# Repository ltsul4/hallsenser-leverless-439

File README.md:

# Magnetic Leverless Controller (自作磁気接点レバーレス)

本プロジェクトは、磁気スイッチ（ホールセンサー）を採用した超低遅延・高機能な競技用レバーレスコントローラーの開発プロジェクトです。

卒業制作の一環として制作されており、進捗に合わせて随時コードやデータの更新を行います。

---

## 概要

従来の物理接点スイッチではなく、磁力による非接触検知を採用することで、物理的な摩耗を抑えつつ、ミリ単位での高度な入力制御を実現しています。

### 主な機能

* **ラピッドトリガー (Rapid Trigger)**
    指の上げ下げに即座に反応する超高速入力を実現。
* **可変作動点 (Actuation Point)**
    反応する深さを 0.1mm 単位でカスタマイズ可能。
* **Web Configurator**
    専用ソフト不要。ブラウザからリアルタイムに設定変更・モニタリングが可能。
* **SOCDクリーナー**
    競技ルールに準拠した同時押し処理（ニュートラル優先、後押し優先等）を実装。
* **コンボボタン機能**
    1つのボタンで複数のボタン同時押しを再現する補助機能（C1～C4）。
* **入力切断機能**
    設定中の誤入力を防ぐためのセーフティ機能。

---

## ハードウェア設計

設計データはすべて `PCB` フォルダ内に格納されています。

* **基板データ (PCB Design)**: 回路図および基板発注用のガーバーデータ。
* **筐体データ (Acrylic Case)**: レーザーカット用のアクリルパネル設計データ。

### 主要コンポーネント

* **MCU**: STM32F303CBT6
* **センサー**: GH39F ホールセンサー
* **スイッチ**: 
    * デフォルト: Gateron Magnetic Jade Ultra (3.2mmストローク)
    * 特別仕様: Gateron Magnetic Jade Pro (3.5mmストローク)
* **マルチプレクサ**: ADG708

> [!NOTE]
> 本リポジトリの標準ファームウェアは **3.2mmストローク (Jade Ultra)** に最適化されています。
> 3.5mmストロークのスイッチを使用する場合は、`main.c` 内の `TRAVEL_DISTANCE_MM` を `3.5f` に変更してビルドしてください。

---

## ディレクトリ構成

*(※必要に応じて追記してください)*

---

## 導入手順

### 1. ファームウェアの書き込み

1.  [STM32CubeProgrammer](https://www.st.com/ja/development-tools/stm32cubeprog.html) をダウンロードしてPCにインストールします。
2.  基板の裏面にある2つのボタンのうち、**上側のBOOTボタンを押しながら**PCとUSBケーブルで接続します。その後、STM32CubeProgrammerを起動します。
3.  画面右側の接続メニューから「USB」を選択し、「Port」のドロップダウンから適切なポート（例: `USB1`）を選んだ後、緑色の**「Connect」**ボタンをクリックして基板と接続します。

4.  接続が成功したら、画面左上の「Open file」タブをクリックします。
5.  ファイル選択ダイアログが開くので、ビルド済みの `.bin` ファイル（例: `Leverless_Controller.bin`）を選択して開きます。

6.  ファイルを読み込んだ後、「Download」ボタンをクリックしてファームウェアの書き込み（インストール）を実行します。
7.  **書き込み完了後、USBケーブルを一度抜き、ボタンを押さずにそのまま再度PCへ接続し直してください。**

### 2. 起動モードの選択

本デバイスには2つの動作モードがあります。

* **ゲームモード (通常起動)**
    そのままUSBを接続します。Windowsから「Xbox 360 Controller」として認識され、すぐにゲームで使用可能です。

* **設定モード (ボタン押下起動)**
    **UPボタン**を押しながらUSBを接続し、**数秒待ってから指を離します**。
    カスタムHIDデバイスとして認識され、ブラウザからの設定が可能になります。

### 3. Web Configurator による設定と使い方

1.  **設定モードで起動**
    前述の通り、UPボタンを押しながらデバイスをPCに接続します。
2.  **ブラウザで設定ページを開く**
    使用しているキースイッチに合わせて、以下のいずれかのページをブラウザ（Chrome/Edge推奨）で開きます。
    * **通常版 (3.2mm / Jade Ultra 等):** [WebDriver.htmlを開く](https://ltsul4.github.io/hallsenser-leverless-439/WebDriver/WebDriver.html)
    * **特別版 (3.5mm / Jade Pro 専用):** [WebDriver3.5.htmlを開く](https://ltsul4.github.io/hallsenser-leverless-439/WebDriver/WebDriver3.5.html)
3.  **デバイスの接続**
    画面右上の「接続」ボタンを押し、リストから該当する端末を選択して接続します。
    > ⚠️ **注意:** 端末選択画面で「Xbox 360 Controller」等の表示が出る場合は、設定モードでの接続が失敗しています。一度ケーブルを抜き、再度UPボタンを確実に押しながらつなぎ直してください。

4.  **各種設定の調整**
    接続が完了すると、専用ドライバー上で以下の設定が可能になります。
    * **キーマッピング:** 各ボタンへの入力割り当てを変更。
    * **入力感度の調整:** Actuation Point (AP: 作動点)、Rapid Trigger (RT: 感度)、Top/Bottom Deadzone (DZ: 指置き・底打ち時の誤爆防止) をスライダーで設定。
    * **リアルタイム動作:** 右下のグラフで、選択したボタン（画像ではUPボタン）のトラッキング状況をリアルタイムに確認。
    * **SOCD設定:** 画面上部のメニューからSOCDクリーナーの方式を選択。

5.  **同時押し設定 (コンボ機能)**
    画面を下にスクロールすると、C1～C4までの4種類の補助ボタンの設定項目があります。ここで複数ボタンの同時押しを登録することができます。
6.  **設定の保存**
    すべての設定が完了したら、画面右上の緑色の**「設定を保存」**ボタンを押します。
7.  **再起動して完了**
    保存完了後、**端末（USBケーブル）を一度抜き、そのまま再度つなぎ直す**ことで、設定がゲームモードに反映されます。

---

## 開発状況

- [x] ホールセンサーによるアナログ値の取得
- [x] ラピッドトリガー・可変作動点アルゴリズムの実装
- [x] WebHID / WebUSB による設定ツールの構築 (`WebDriver.html`)
- [x] Flashメモリへの設定保存機能
- [x] 同時押し（コンボ）ボタン機能の実装

---

## クレジット・参考元

本プロジェクトの制作にあたり、以下のプロジェクトを参考にさせていただきました。
* **参考元:** [kenyoshizoe/ember](https://github.com/kenyoshizoe/ember)

また、本プロジェクトのコードおよびドキュメントの一部は、**Gemini** を活用して作成されました。

---

## ライセンス

**MIT License**

本プロジェクトは卒業制作として継続的に開発されています。温かい目で見守っていただければ幸いです。

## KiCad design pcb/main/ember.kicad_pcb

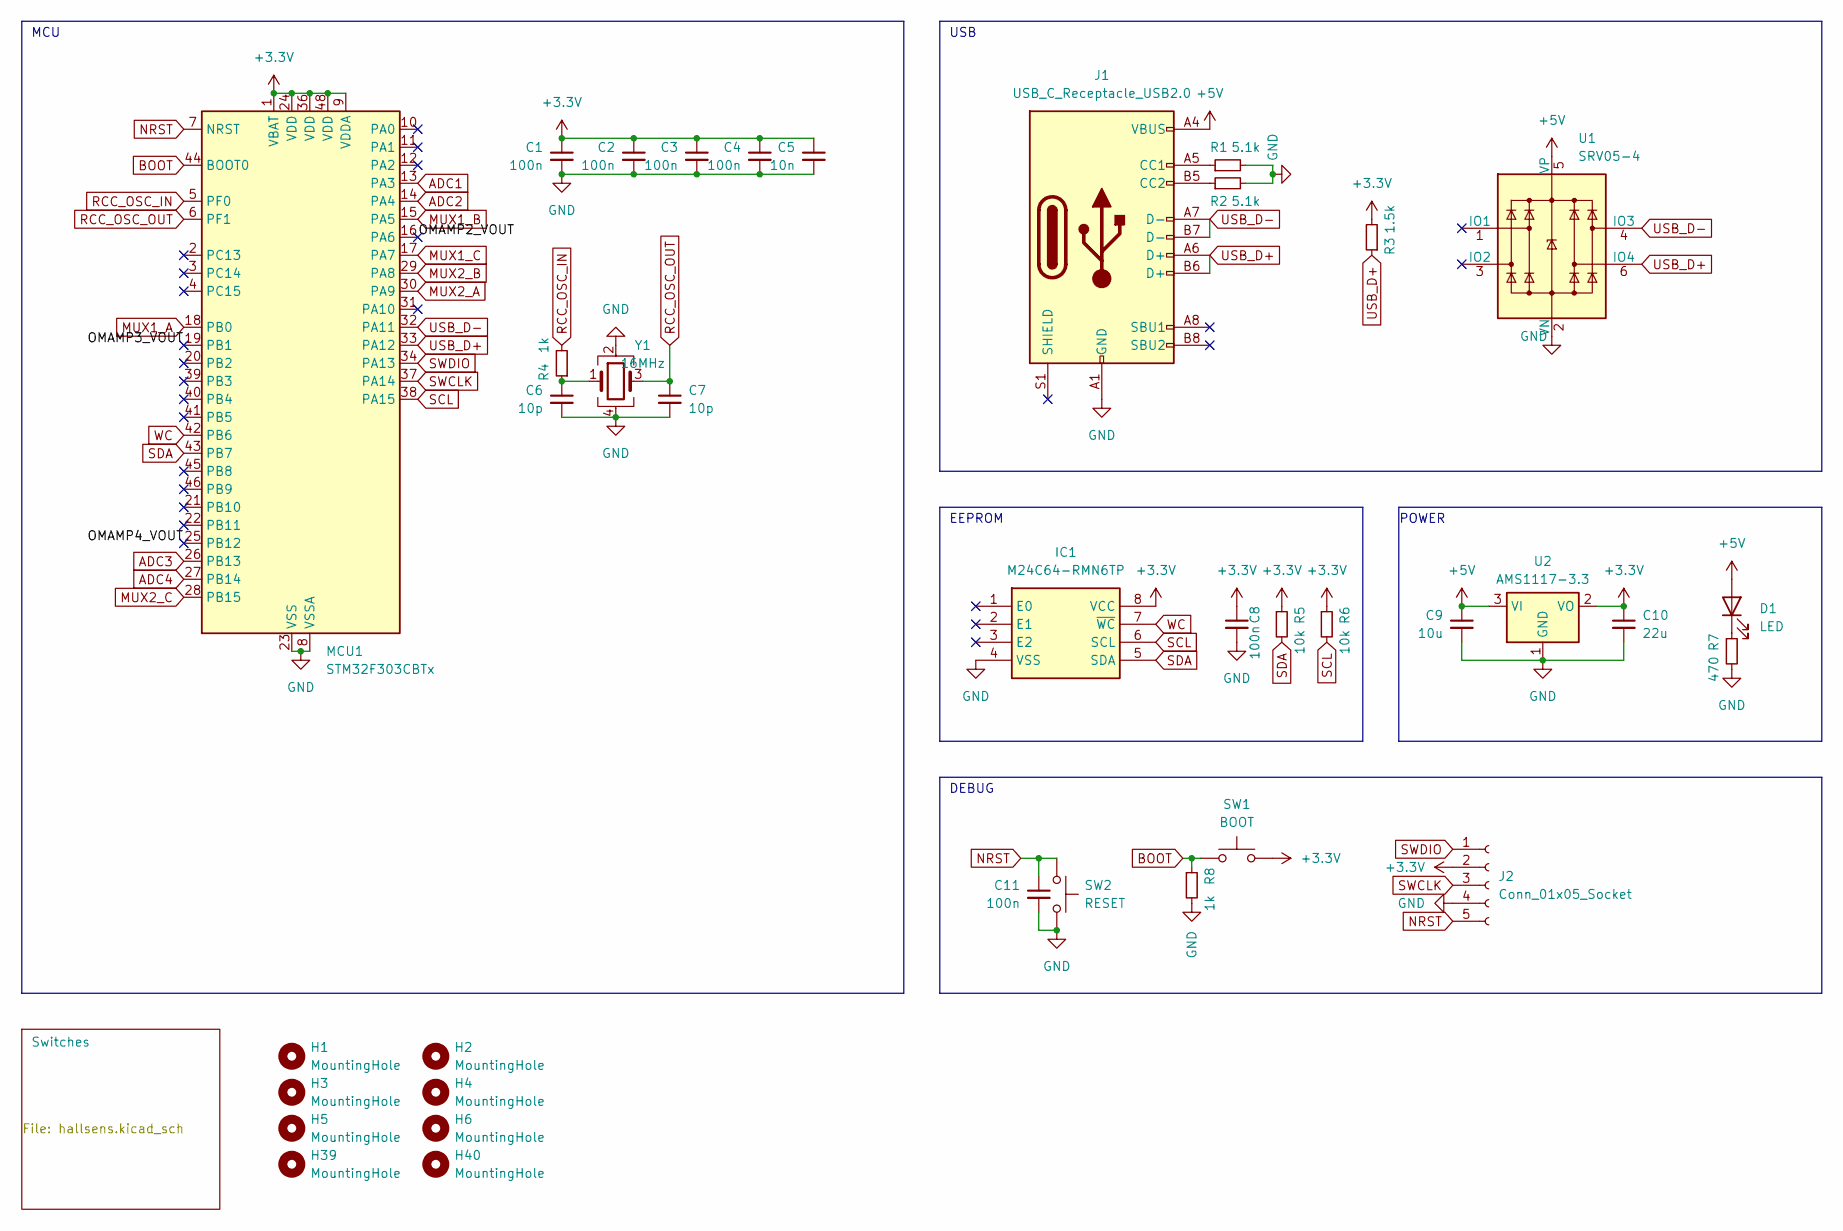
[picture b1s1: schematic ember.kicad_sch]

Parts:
C1, C2, C3, C4, C8, C11: 100n; C_0603_1608Metric; LCSC C14663
C5: 10n; C_0603_1608Metric; LCSC C57112
C6, C7: 10p; C_0603_1608Metric; LCSC C1634
C9: 10u; C_0603_1608Metric; LCSC C19702
C10: 22u; C_0603_1608Metric; LCSC C59461
D1: LED; LED_0603_1608Metric; LCSC C72043
H1, H2, H3, H4, H5, H6, H39, H40: MountingHole; MountingHole_2.2mm_M2
IC1: M24C64-RMN6TP; SOIC127P600X175-8N; Mouser Part Number 511-M24C64-RMN6TP
J1: USB_C_Receptacle_USB2.0; USB_C_Receptacle_XKB_U262-16XN-4BVC11; LCSC C319148
J2: Conn_01x05_Socket; PinSocket_1x05_P2.54mm_Vertical
MCU1: STM32F303CBTx; LQFP-48_7x7mm_P0.5mm; LCSC C108516
R1, R2: 5.1k; R_0603_1608Metric; LCSC C23186
R3: 1.5k; R_0603_1608Metric; LCSC C22843
R4, R8: 1k; R_0603_1608Metric; LCSC C21190
R5, R6: 10k; R_0603_1608Metric; LCSC C25804
R7: 470; R_0603_1608Metric; LCSC C23179
SW1: BOOT; SW_Push_1P1T_XKB_TS-1187A; LCSC C318884
SW2: RESET; SW_Push_1P1T_XKB_TS-1187A; LCSC C318884
U1: SRV05-4; SOT-23-6; LCSC C85364
U2: AMS1117-3.3; SOT-223-3_TabPin2; LCSC C6186
Y1: 16MHz; Crystal_SMD_3225-4Pin_3.2x2.5mm; LCSC C13738

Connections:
+3.3V: C1.1, C2.1, C3.1, C4.1, C5.1, C8.1, C10.1, IC1.8 (VCC), J2.2, MCU1.1 (VBAT), MCU1.9 (VDDA), MCU1.24 (VDD), MCU1.36 (VDD), MCU1.48 (VDD), R3.2, R5.1, R6.1, SW1.2, U2.2 (VO); also elsewhere on the board
+5V: C9.1, D1.2 (A), J1.A4 (VBUS), J1.A9 (VBUS), J1.B4 (VBUS), J1.B9 (VBUS), U1.5 (VP), U2.3 (VI)
/OMAMP2_VOUT: MCU1.16 (PA6)
/OMAMP3_VOUT: MCU1.19 (PB1)
/OMAMP4_VOUT: MCU1.25 (PB12)
ADC1: MCU1.13 (PA3)
ADC2: MCU1.14 (PA4); also elsewhere on the board
ADC3: MCU1.26 (PB13); also elsewhere on the board
ADC4: MCU1.27 (PB14); also elsewhere on the board
BOOT: MCU1.44 (BOOT0), R8.1, SW1.1
GND: C1.2, C2.2, C3.2, C4.2, C5.2, C6.2, C7.2, C8.2, C9.2, C10.2, C11.2, IC1.4 (VSS), J1.A1 (GND), J1.A12 (GND), J1.B1 (GND), J1.B12 (GND), J2.4, MCU1.8 (VSSA), MCU1.23 (VSS), MCU1.35 (VSS), MCU1.47 (VSS), R1.2, R2.2, R7.2, R8.2, SW2.2, U1.2 (VN), U2.1 (GND), Y1.2, Y1.4; also elsewhere on the board
MUX1_A: MCU1.18 (PB0); also elsewhere on the board
MUX1_B: MCU1.15 (PA5); also elsewhere on the board
MUX1_C: MCU1.17 (PA7); also elsewhere on the board
MUX2_A: MCU1.30 (PA9); also elsewhere on the board
MUX2_B: MCU1.29 (PA8); also elsewhere on the board
MUX2_C: MCU1.28 (PB15); also elsewhere on the board
NRST: C11.1, J2.5, MCU1.7 (NRST), SW2.1
unnamed: C6.1, R4.1, Y1.1
unnamed: D1.1 (K), R7.1
unnamed: J1.A5 (CC1), R1.1
unnamed: J1.B5 (CC2), R2.1
RCC_OSC_IN: MCU1.5 (PF0), R4.2
RCC_OSC_OUT: C7.1, MCU1.6 (PF1), Y1.3
SCL: IC1.6 (SCL), MCU1.38 (PA15), R6.2
SDA: IC1.5 (SDA), MCU1.43 (PB7), R5.2
SWCLK: J2.3, MCU1.37 (PA14)
SWDIO: J2.1, MCU1.34 (PA13)
USB_D+: J1.A6 (D+), J1.B6 (D+), MCU1.33 (PA12), R3.1, U1.6 (IO4)
USB_D-: J1.A7 (D-), J1.B7 (D-), MCU1.32 (PA11), U1.4 (IO3)
WC: IC1.7 (~WC), MCU1.42 (PB6)

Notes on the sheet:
MCU
USB
POWER
EEPROM
DEBUG

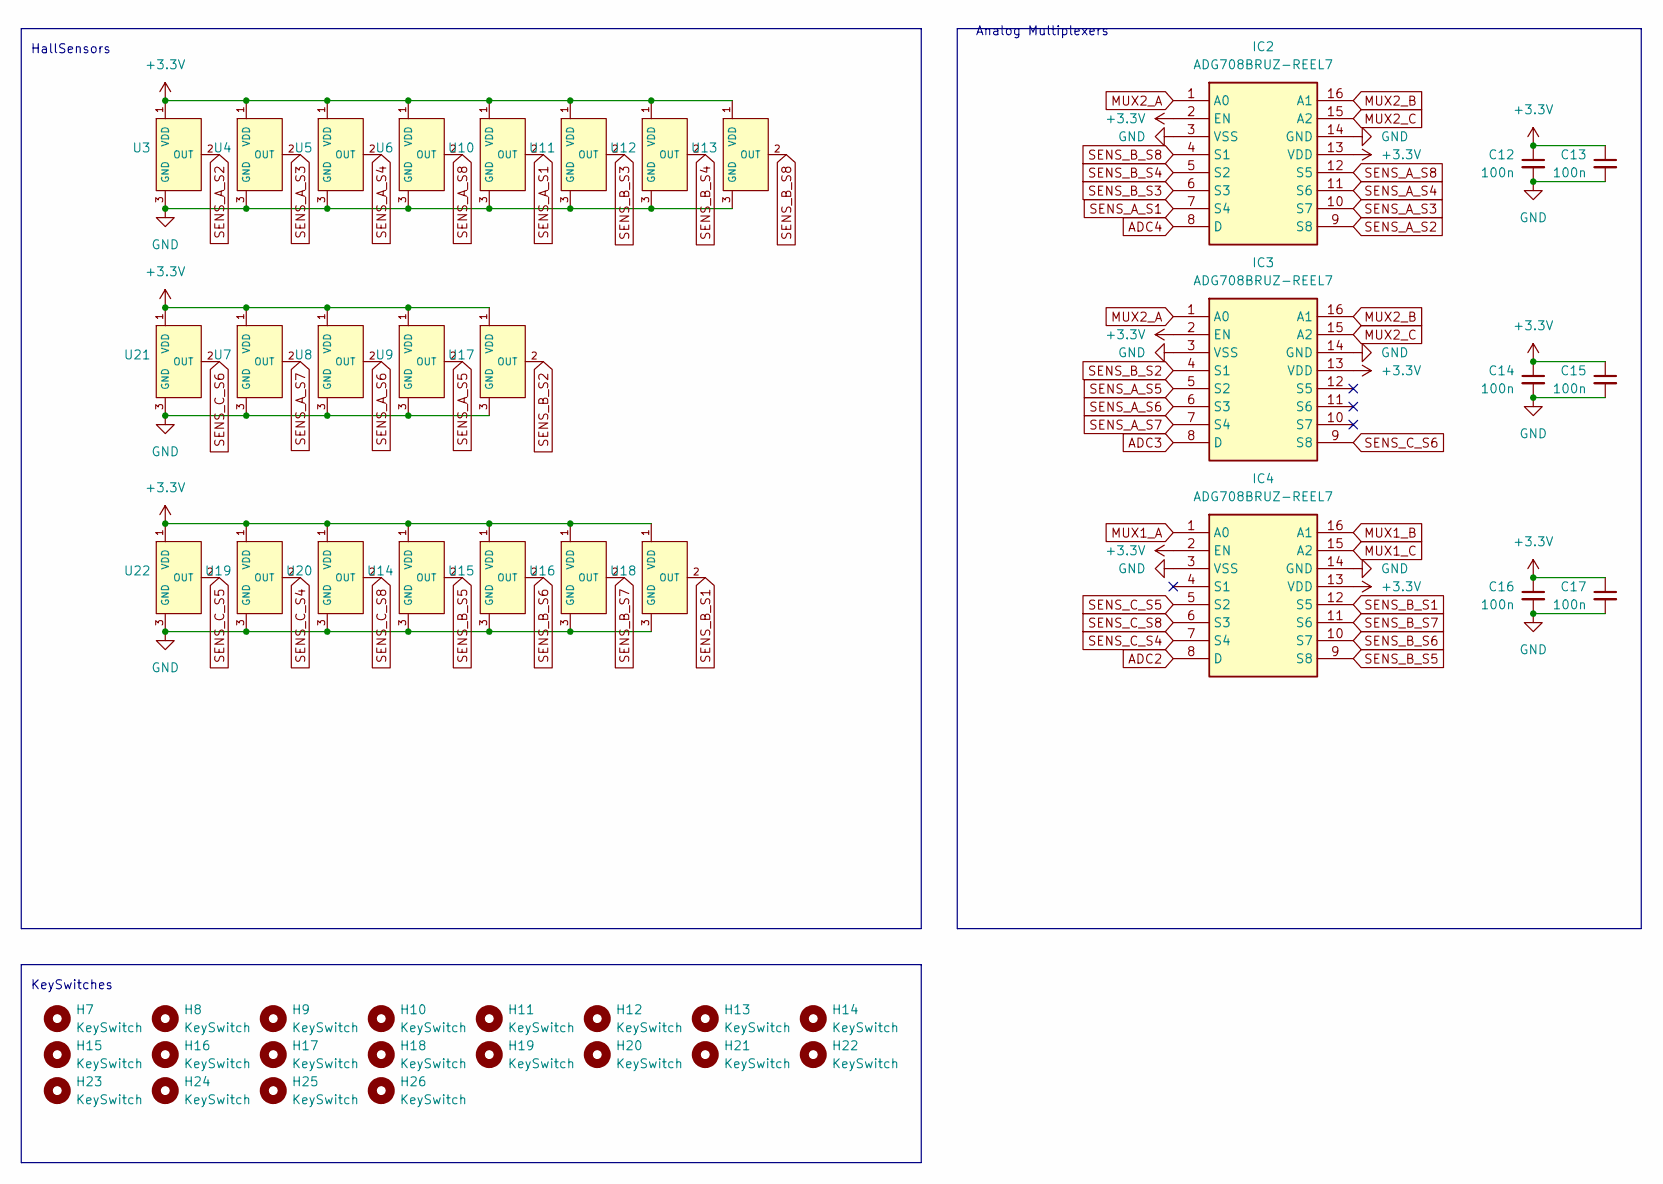
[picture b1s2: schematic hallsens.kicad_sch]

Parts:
C12, C13, C14, C15, C16, C17: 100n; C_0603_1608Metric; LCSC C14663
H7, H8, H9, H10, H11, H12, H13, H14, H15, H16, H17, H18, H19, H20, H21, H22, H23, H24, H25, H26: KeySwitch; MX-1U-NoPins
IC2, IC3, IC4: ADG708BRUZ-REEL7; SOP65P640X120-16N; Mouser Part Number 584-ADG708BRUZ-R7
U3, U4, U5, U6, U7, U8, U9, U10, U11, U12, U13, U14, U15, U16, U17, U18, U19, U20, U21, U22: Hall_Sensor; SOT-23; MPN SLSS49E-3; LCSC Part C266230

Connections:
+3.3V: C12.1, C13.1, C14.1, C15.1, C16.1, C17.1, IC2.2 (EN), IC2.13 (VDD), IC3.2 (EN), IC3.13 (VDD), IC4.2 (EN), IC4.13 (VDD), U3.1 (VDD), U4.1 (VDD), U5.1 (VDD), U6.1 (VDD), U7.1 (VDD), U8.1 (VDD), U9.1 (VDD), U10.1 (VDD), U11.1 (VDD), U12.1 (VDD), U13.1 (VDD), U14.1 (VDD), U15.1 (VDD), U16.1 (VDD), U17.1 (VDD), U18.1 (VDD), U19.1 (VDD), U20.1 (VDD), U21.1 (VDD), U22.1 (VDD); also elsewhere on the board
ADC2: IC4.8 (D); also elsewhere on the board
ADC3: IC3.8 (D); also elsewhere on the board
ADC4: IC2.8 (D); also elsewhere on the board
GND: C12.2, C13.2, C14.2, C15.2, C16.2, C17.2, IC2.3 (VSS), IC2.14 (GND), IC3.3 (VSS), IC3.14 (GND), IC4.3 (VSS), IC4.14 (GND), U3.3 (GND), U4.3 (GND), U5.3 (GND), U6.3 (GND), U7.3 (GND), U8.3 (GND), U9.3 (GND), U10.3 (GND), U11.3 (GND), U12.3 (GND), U13.3 (GND), U14.3 (GND), U15.3 (GND), U16.3 (GND), U17.3 (GND), U18.3 (GND), U19.3 (GND), U20.3 (GND), U21.3 (GND), U22.3 (GND); also elsewhere on the board
MUX1_A: IC4.1 (A0); also elsewhere on the board
MUX1_B: IC4.16 (A1); also elsewhere on the board
MUX1_C: IC4.15 (A2); also elsewhere on the board
MUX2_A: IC2.1 (A0), IC3.1 (A0); also elsewhere on the board
MUX2_B: IC2.16 (A1), IC3.16 (A1); also elsewhere on the board
MUX2_C: IC2.15 (A2), IC3.15 (A2); also elsewhere on the board
SENS_A_S1: IC2.7 (S4), U10.2 (OUT)
SENS_A_S2: IC2.9 (S8), U3.2 (OUT)
SENS_A_S3: IC2.10 (S7), U4.2 (OUT)
SENS_A_S4: IC2.11 (S6), U5.2 (OUT)
SENS_A_S5: IC3.5 (S2), U9.2 (OUT)
SENS_A_S6: IC3.6 (S3), U8.2 (OUT)
SENS_A_S7: IC3.7 (S4), U7.2 (OUT)
SENS_A_S8: IC2.12 (S5), U6.2 (OUT)
SENS_B_S1: IC4.12 (S5), U18.2 (OUT)
SENS_B_S2: IC3.4 (S1), U17.2 (OUT)
SENS_B_S3: IC2.6 (S3), U11.2 (OUT)
SENS_B_S4: IC2.5 (S2), U12.2 (OUT)
SENS_B_S5: IC4.9 (S8), U14.2 (OUT)
SENS_B_S6: IC4.10 (S7), U15.2 (OUT)
SENS_B_S7: IC4.11 (S6), U16.2 (OUT)
SENS_B_S8: IC2.4 (S1), U13.2 (OUT)
SENS_C_S4: IC4.7 (S4), U19.2 (OUT)
SENS_C_S5: IC4.5 (S2), U22.2 (OUT)
SENS_C_S6: IC3.9 (S8), U21.2 (OUT)
SENS_C_S8: IC4.6 (S3), U20.2 (OUT)

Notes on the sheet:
KeySwitches
HallSensors
Analog Multiplexers

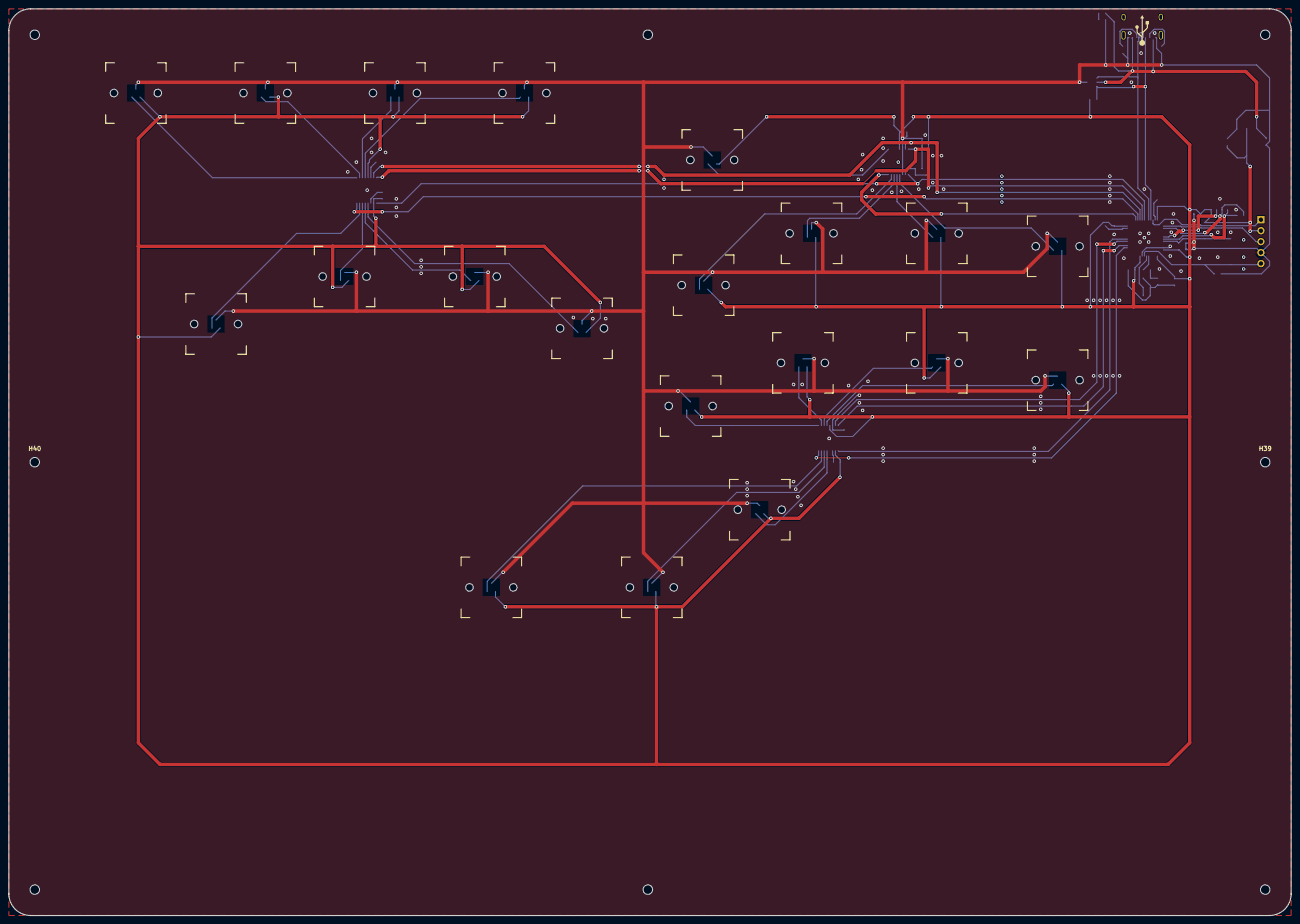
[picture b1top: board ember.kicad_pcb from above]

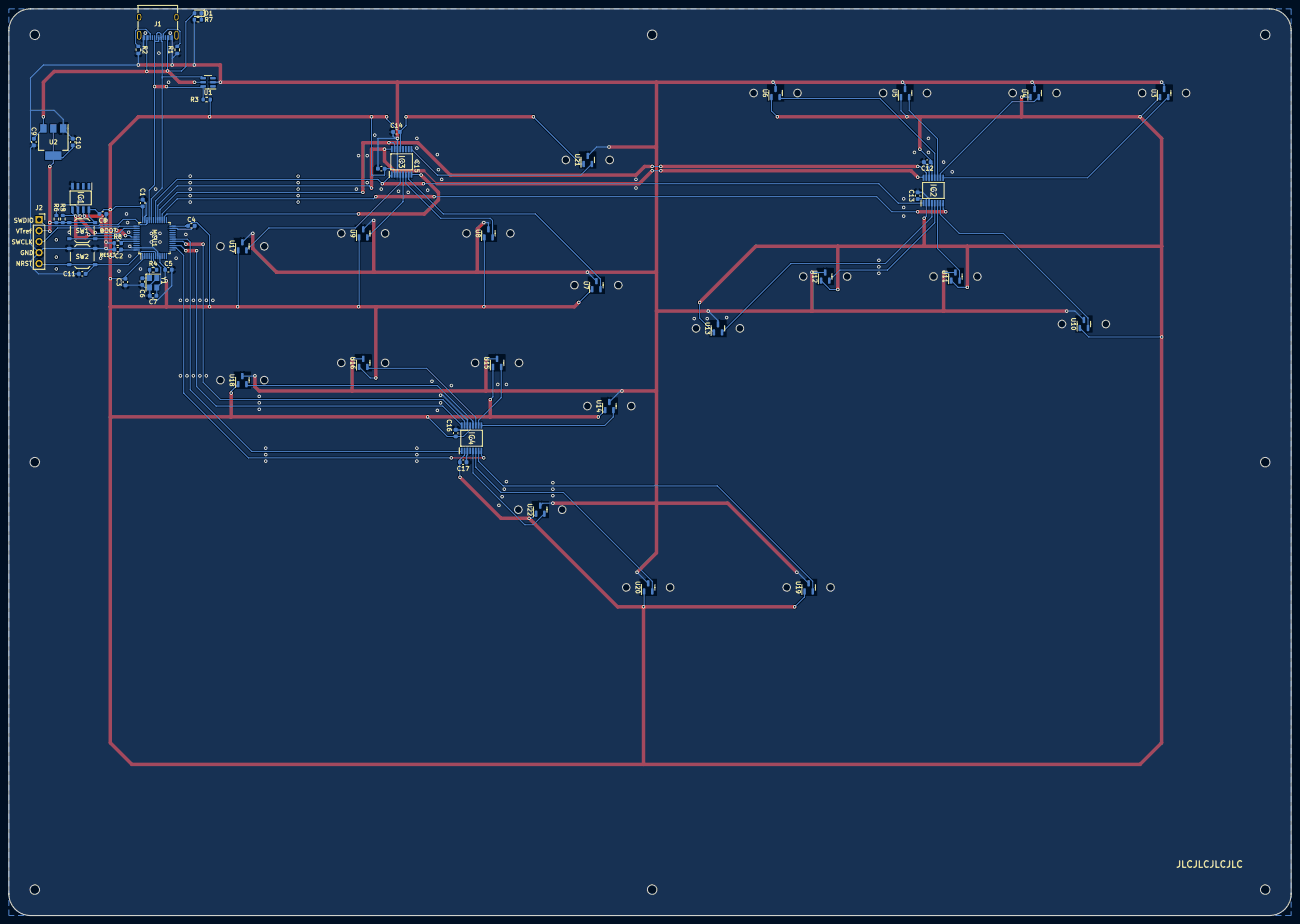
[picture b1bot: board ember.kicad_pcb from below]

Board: 2 copper layers, 297.0 x 210.0 mm, 86 parts (58 on the bottom side), 47 nets.

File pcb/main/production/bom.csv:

Designator,Footprint,Quantity,Value,LCSC Part #
"C1, C11, C12, C13, C14, C15, C16, C17, C2, C3, C4, C8",0603,12,100n,C14663
C10,0603,1,22u,C59461
C5,0603,1,10n,C57112
"C6, C7",0603,2,10p,C1634
C9,0603,1,10u,C19702
D1,0603,1,LED,C72043
"H1, H2, H3, H39, H4, H40, H5, H6",MountingHole_2.2mm_M2,8,MountingHole,
"H10, H11, H12, H13, H14, H15, H16, H17, H18, H19, H20, H21, H22, H23, H24, H25, H26, H7, H8, H9",MX-1U-NoPins,20,KeySwitch,
IC1,SOIC127P600X175-8N,1,M24C64-RMN6TP,C79988
"IC2, IC3, IC4",SOP65P640X120-16N,3,ADG708BRUZ-REEL7,C35325
J1,USB_C_Receptacle_XKB_U262-16XN-4BVC11,1,USB_C_Receptacle_USB2.0,C319148
J2,PinSocket_1x05_P2.54mm_Vertical,1,Conn_01x05_Socket,
MCU1,LQFP-48_7x7mm_P0.5mm,1,STM32F303CBTx,C108516
"R1, R2",0603,2,5.1k,C23186
R3,0603,1,1.5k,C22843
"R4, R8",0603,2,1k,C21190
"R5, R6",0603,2,10k,C25804
R7,0603,1,470,C23179
SW1,SW_Push_1P1T_XKB_TS-1187A,1,BOOT,C318884
SW2,SW_Push_1P1T_XKB_TS-1187A,1,RESET,C318884
U1,SOT-23-6,1,SRV05-4,C85364
"U10, U11, U12, U13, U14, U15, U16, U17, U18, U19, U20, U21, U22, U3, U4, U5, U6, U7, U8, U9",SOT-23,20,Hall_Sensor,C266230
U2,SOT-223-3_TabPin2,1,AMS1117-3.3,C6186
Y1,Crystal_SMD_3225-4Pin_3.2x2.5mm,1,16MHz,C13738

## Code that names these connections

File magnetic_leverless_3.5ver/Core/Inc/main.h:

/* USER CODE BEGIN Header */
/**
  ******************************************************************************
  * @file           : main.h
  * @brief          : Header for main.c file.
  *                   This file contains the common defines of the application.
  ******************************************************************************
  * @attention
  *
  * Copyright (c) 2025 STMicroelectronics.
  * All rights reserved.
  *
  * This software is licensed under terms that can be found in the LICENSE file
  * in the root directory of this software component.
  * If no LICENSE file comes with this software, it is provided AS-IS.
  *
  ******************************************************************************
  */
/* USER CODE END Header */

/* Define to prevent recursive inclusion -------------------------------------*/
#ifndef __MAIN_H
#define __MAIN_H

#ifdef __cplusplus
extern "C" {
#endif

/* Includes ------------------------------------------------------------------*/
#include "stm32f3xx_hal.h"

/* main.h の中に追加 */
extern uint8_t g_boot_mode; // 0: Xbox, 1: Config

/* Private includes ----------------------------------------------------------*/
/* USER CODE BEGIN Includes */

/* USER CODE END Includes */

/* Exported types ------------------------------------------------------------*/
/* USER CODE BEGIN ET */

/* USER CODE END ET */

/* Exported constants --------------------------------------------------------*/
/* USER CODE BEGIN EC */

/* USER CODE END EC */

/* Exported macro ------------------------------------------------------------*/
/* USER CODE BEGIN EM */

/* USER CODE END EM */

/* Exported functions prototypes ---------------------------------------------*/
void Error_Handler(void);

/* USER CODE BEGIN EFP */

/* USER CODE END EFP */

/* Private defines -----------------------------------------------------------*/
#define MUX1_B_Pin GPIO_PIN_5
#define MUX1_B_GPIO_Port GPIOA
#define MUX1_C_Pin GPIO_PIN_7
#define MUX1_C_GPIO_Port GPIOA
#define MUX1_A_Pin GPIO_PIN_0
#define MUX1_A_GPIO_Port GPIOB
#define MUX2_C_Pin GPIO_PIN_15
#define MUX2_C_GPIO_Port GPIOB
#define MUX2_B_Pin GPIO_PIN_8
#define MUX2_B_GPIO_Port GPIOA
#define MUX2_A_Pin GPIO_PIN_9
#define MUX2_A_GPIO_Port GPIOA
#define USB_D__Pin GPIO_PIN_11
#define USB_D__GPIO_Port GPIOA
#define USB_D_A12_Pin GPIO_PIN_12
#define USB_D_A12_GPIO_Port GPIOA
#define SWDIO_Pin GPIO_PIN_13
#define SWDIO_GPIO_Port GPIOA
#define SWCLK_Pin GPIO_PIN_14
#define SWCLK_GPIO_Port GPIOA
#define SCL_Pin GPIO_PIN_15
#define SCL_GPIO_Port GPIOA
#define WC_Pin GPIO_PIN_6
#define WC_GPIO_Port GPIOB
#define SDA_Pin GPIO_PIN_7
#define SDA_GPIO_Port GPIOB

/* USER CODE BEGIN Private defines */

/* USER CODE END Private defines */

#ifdef __cplusplus
}
#endif

#endif /* __MAIN_H */

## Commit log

2026-02-17 完成版Ver1.0
2026-02-18 完全版Ver1.1
2026-02-18 Ver1.2訂正版
2026-02-18 readme編集
2026-02-18 特別仕様
2026-02-19 Rename magnetic_leverless_3.5ver/WebDriver/WebDriver.html to magnetic_leverless_3.5ver/index3.5.html
2026-02-19 Rename WebDriver.html to index.html
2026-02-19 Rename magnetic_leverless/WebDriver/index.html to WebDriver.html
2026-02-19 名称変更
2026-02-26 最終調整
2026-02-26 SN調整
2026-02-26 天板用画像追加
